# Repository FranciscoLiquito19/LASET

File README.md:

# LASET

Relatório de Laboratório de Sistemas Autónomos: **Sistema de Escrita/Leitura Multi-Protocolo**, com I2C, RS232, RS485, dois CAN FD,
Ethernet, três saídas PWM isoladas e sincronização por PPS/GPS.

Autores: Francisco Liquito e Pedro Ribeiro. Ano letivo: 2026/2027.

## Compilar

O único relatório oficial tem como ficheiro principal
`template_laset/Modelo_LaSET.tex`.
Instalar uma distribuição LaTeX com os pacotes usados nesse ficheiro, além de
`latexmk` e BibTeX. A bibliografia mantém o estilo `unsrt` do template.
Os diagramas vetoriais são compilados diretamente com TikZ/PGF, usando
os estilos comuns de `template_laset/Outros/Estilo_Visual.tex`.

```sh
cd template_laset
mkdir -p build
latexmk -pdf \
  -outdir=build \
  -interaction=nonstopmode \
  -halt-on-error \
  -file-line-error \
  Modelo_LaSET.tex
```

O PDF é gerado em `template_laset/build/Modelo_LaSET.pdf` (caminho relativo à raiz do
repositório). O `latexmk` executa pdfLaTeX, BibTeX e as passagens necessárias
para resolver as citações e os índices.

No VS Code, a receita existente do LaTeX Workshop usa
`"latex-workshop.latex.outDir": "%DIR%/build"` e passa esse diretório ao
`latexmk` através de `-outdir=%OUTDIR%`. Ao compilar o ficheiro principal,
o resultado fica no mesmo caminho indicado acima. O PDF oficial é versionado;
os ficheiros auxiliares de compilação em `build/` são ignorados pelo Git.

A fase do relatório escolhe-se em `template_laset/Outros/Identificacao.tex`
(`\Requisitostrue`, `\Projectotrue`, `\Finalfalse` na fase atual, de Projeto), onde
estão também o título e a data da capa (`\DataRelatorio`, a atualizar em cada entrega).
O Anexo A inclui o esquema elétrico diretamente de `hardware/laset_gateway.pdf`.

## Estrutura

- `template_laset/Modelo_LaSET.tex`: ficheiro principal do único relatório oficial.
- `template_laset/Capitulos/`: conteúdo organizado pelos capítulos oficiais.
- `template_laset/Outros/Identificacao.tex`: fase, título e autores.
- `template_laset/Figuras/`: imagens utilizadas no relatório.
- `template_laset/Figuras/diagramas/`: fontes TikZ dos esquemas e gráficos temporais.
- `template_laset/Anexos/`: conteúdo dos anexos.
- `template_laset/bibliografia.bib`: referências bibliográficas em BibTeX.
- `template_laset/build/`: PDF oficial versionado e auxiliares de compilação ignorados pelo Git.
- `hardware/`: projeto KiCad gerado por código (`hardware/gerador`): esquema, placa de
  quatro camadas (disposição e planos feitos, encaminhamento de sinais por fazer) e lista
  de material em `hardware/bom/bom.csv`; ver o [README do hardware](hardware/README.md).
- `firmware/`: firmware do STM32H7 com FreeRTOS (CMake); ver o [README do firmware](firmware/README.md).
- `.github/workflows/ci.yml`: compila o relatório, verifica o esquema, corre o ERC e o DRC
  do KiCad 9 (com paridade esquema/placa), compila o firmware e corre os testes em cada
  push e pull request.
- `.vscode/settings.json`: configuração de compilação do LaTeX Workshop.

As [notas da revisão](docs/revisao_final.md) incluem os resultados de
validação e um roteiro para leitura conjunta do PDF.

## Apresentação e guião

- [PowerPoint atualizado](apresentacao/output/Apresentacao_LaSET_Integracao_Robotica_Revista.pptx): 10 slides centrados na integração de equipamentos em sistemas robóticos, com fundamentos, estado da arte, casos de utilização, requisitos, arquitetura e verificação prevista.
- [Guião em PDF](apresentacao/output/Guiao_Apresentacao.pdf) e [fonte editável](apresentacao/Guiao_Apresentacao.md): divisão entre Pedro e Francisco Liquito, falas, tempos e perguntas de preparação.

RF17 distingue os quatro pares mínimos obrigatórios com Ethernet dos
percursos adicionais que podem ser definidos e implementados em projeto.
Os critérios de ensaio abrangem todos os percursos efetivamente definidos.

A versão de 29 de outubro acompanha um cenário ilustrativo com motor,
bateria e sensor. A reutilização em diferentes sistemas é um objetivo;
funcionamento em óleo e sob pressão permanece uma possibilidade futura,
com condições e validação por definir. O guião acompanha esta versão,
com Pedro nos slides 1 a 5 e Francisco Liquito nos slides 6 a 10,
numa duração de ensaio de cerca de nove minutos.

## Trabalhar em conjunto

Após receber acesso ao repositório, clonar o projeto:

```sh
git clone https://github.com/FranciscoLiquito19/LASET.git
cd LASET
```

Na primeira vez, em cada computador, configurar o autor dos commits (sem isto aparecem
commits com autor «unknown»):

```sh
git config user.name "Nome Apelido"
git config user.email "email@exemplo.pt"
```

Antes de começar uma alteração, atualizar a cópia local e criar um ramo:

```sh
git pull --ff-only
git switch -c descricao-da-alteracao
```

Depois de editar e compilar, guardar apenas os ficheiros pretendidos e publicar o ramo:

```sh
git add template_laset/ hardware/ README.md
git commit -m "Descrever a alteração"
git push -u origin descricao-da-alteracao
```

No GitHub, abrir um pull request para rever e integrar a alteração no ramo principal
(`master`). Só integrar depois de a verificação automática (CI) passar. Usar um nome diferente para cada novo ramo.

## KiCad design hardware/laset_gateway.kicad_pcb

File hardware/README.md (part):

# Hardware do gateway LASET

Projeto KiCad do gateway multiprotocolo. O esquema é **gerado por código** a partir de
`gerador/`: cada folha é um ficheiro Python com os componentes, os valores e a rede de
cada pino. Assim cada alteração fica revista em PR, como o relatório.

## Abrir o projeto (esquema e placa)

1. Abrir `laset_gateway.kicad_pro` no KiCad (8 ou 9). Se perguntar se quer atualizar o
   formato dos ficheiros, aceitar: o gerador escreve no formato do KiCad 6/7.
2. No editor de esquemas, a folha raiz mostra uma caixa por folha. Duplo clique entra
   na folha.
3. As ligações são feitas por **etiquetas** (texto junto a cada pino) e por símbolos de
   alimentação (GND, +5V, +3V3). Dois pinos com a mesma etiqueta estão ligados.
   Etiquetas com forma de seta são globais e ligam entre folhas.

## Verificar

1. `python3 -I gerador/verificar.py` (precisa do `kicad-cli`): exporta a netlist e falha se
   houver redes com um só pino ou sinais globais que não saem da folha onde nascem.
   Apanha etiquetas mal escritas e pinos esquecidos.
2. No KiCad: `Inspecionar > Verificador de regras elétricas > Executar ERC`. Os pinos sem
   ligação devem ser só os marcados com cruz (NC do LM5177, HO1_LL/HO2_LL, GPIO livres do
   MCU, LEDs do RJ45, sinais auxiliares dos transceivers). Qualquer outro erro deve ser
   reportado. O ERC não corre na linha de comandos do KiCad 7; no 8 ou 9:
   `kicad-cli sch erc laset_gateway.kicad_sch`.

## Regenerar depois de mudar o código

```sh
cd hardware/gerador
python3 -I gerar.py
python3 -I verificar.py
kicad-cli sch export pdf -o ../laset_gateway.pdf ../laset_gateway.kicad_sch
```

O Anexo A do relatório lê este PDF diretamente; basta recompilar o relatório.

O `gerar.py` recusa referências repetidas entre folhas. Não editar à mão os
`.kicad_sch` gerados: as alterações perdem-se na próxima geração. Arrumar a posição dos
componentes na interface é seguro só depois de congelarmos o gerador (fase de layout).

## Placa de circuito impresso (`laset_gateway.kicad_pcb`)

Também é gerada por código, em dois passos, a partir do esquema:

```sh
cd hardware/gerador
python3 pcb.py       # placa, disposição, planos e regras (refaz a placa de raiz)
python3 fanout.py    # vias dos pinos de massa e alimentação para os planos
python3 curtas.py    # rascunho: ligações de sinal curtas (F.Cu, ou B.Cu com duas vias)
python3 encaminhar.py   # rascunho: encaminhador em grelha (A*) para o resto, com vias
```

Ordem usada para a placa atual (refeita a 25 e 26/11 depois da revisão independente):

```sh
python3 pcb.py && python3 fanout.py      # 302 ligações por fazer
python3 pf.py                            # encaminhamento por congestionamento negociado (~60 min): 80
python3 encaminhar.py && FINO=1 python3 encaminhar.py               # 28 -> 21
VIA=0.5 python3 interior.py              # F.Cu + In2 (sinais lentos) e F/B com HV: 21 -> 16
python3 melhorar.py <base>               # pesquisa local (base = placa depois de fanout.py): 16 -> 12
VIA=0.5 BASE=<base> python3 interior.py  # com arranque: 12 -> 11
# fecho por coordenadas e arrancar_e_ordenar() (ver abaixo): 11 -> 0
python3 serigrafia.py                    # referências sem sobreposição e nome dos conectores
# 26/11, depois da revisão:
python3 vias_pad.py && REDUZIR=1 python3 vias_pad.py   # vias fora dos pads: 90 -> 12
python3 baixo.py C62:U5.4 C63:U5.4 C61:U5.3            # desacoplamento do U5 para B.Cu
# VCAP do STM32 (C34, C35) para B.Cu, arrancando e voltando a encaminhar as redes à volta
python3 limpar.py                        # retira pistas com uma ponta solta
python3 pilha.py                         # pilha JLC04161H-7628 no ficheiro da placa
python3 vista3d.py                       # texturas e componentes para hardware/3d/index.html
```

As últimas 11 foram fechadas com pistas e vias postas por coordenadas (afastamento
verificado à mão e depois pelo DRC) ou arrancando e voltando a encaminhar só as redes
vizinhas:

- LM5177: SW2 do pino ao C10 e à zona SW2 por B.Cu, à volta da diagonal do HO2; LA, EN e VIN
  pelo `interior.py` com a área `lm5177` (ver abaixo).
- LAN8742A: via de 0,5 mm do +3V3 do pino 30.25 em (79,1; 30,4), com o GND do C41 a partilhar
  a via do C48; NRST, TX_EN e TXD0 descem em paralelo pelo corredor entre C44 e C42; TXP em
  F.Cu entre RXN e TXN até baixo do R37 e depois por B.Cu entre as resistências de terminação
  (a via do TXN desceu 0,35 mm para lhe dar passagem). R32 saiu do esquema: o REGOFF tem
  pull-down interno e a flutuar o regulador de 1,2 V fica ligado (folha do LAN8742A, 3.7.3.2).
- STM32: I2C1_SCL e GPS_TX com o vizinho (SDA, RX) arrancado e encaminhado depois.
- ETH_REF_CLK: tem 33 Ω em série junto ao PHY (R94). Ao refazer a zona do VCAP (26/11)
  saiu de In2: passa agora por F.Cu (37 mm) e B.Cu (3 mm), com 4 vias.

Área `lm5177`: área de regra sem restrições à volta do LM5177 e dos seus passivos (x 30 a
50, y 26 a 42). Lá dentro a classe HV usa 0,15 mm em vez de 0,6 mm (`.kicad_dru`): sob
máscara de solda, 0,13 mm chegam até 100 V (IPC-2221B, B4). O `interior.py` usa o mesmo
afastamento na grelha.

O `interior.py` usa a camada In2 (plano de 3,3 V) para sinais lentos: cada pista em In2
recorta o plano. Não podem ir para In2 as classes HV e P5V (nós de comutação e potência), a
classe ETH (pares) nem o REF_CLK, a não ser por exceção explícita. As vias de saída são de
0,5/0,2 mm (anel de 0,15 mm) com pelo menos 0,8 mm entre centros. Estão em In2: GPS_TX
(35 mm), GPS_RX (27 mm), CAN1_TX (27 mm), I2C_OE (19 mm), RS485_TX (7 mm) e RBIAS (4 mm),
todos lentos (UART, CAN a 1 Mbit/s no máximo, níveis estáticos). Com a pilha JLC04161H-7628
(`pilha.py`), In2 fica a 0,21 mm de B.Cu e a 1,07 mm de In1: a referência destas pistas é o
plano de 3,3 V à volta e o cobre de B.Cu, não o plano de massa.

Vias e pads (`vias_pad.py`, 26/11): uma via não tapada dentro de um pad, ou encostada a ele,
puxa a solda para o furo e a junta fica fraca. Os encaminhadores deixaram 90 assim; 78 foram
mudadas para o sítio livre mais perto (fora do pad, 0,1 mm de folga) com uma pista curta, 7
delas com 0,5/0,2 mm para caber. Ficam 11 sem lugar, mesmo com pistas em L e 5 mm de busca
(`EM_L=1 REDUZIR=1`): VCC do LM5177, os VISOOUT e o RS485 do lado isolado do U7, CANH1 no D4,
VDDCR no C44, PWM_FALHA no R86 e o +3V3 do U6. Na encomenda, pedir vias cheias e tapadas
("Epoxy Filled & Capped"), que resolve estas 11 sem mexer na placa. Uma via perto de um pad
sem lhe tocar fica tapada pela máscara (é o normal no KiCad) e não conta. As vias dos pads
térmicos (Q1 a Q4) ficam, como é normal.

Desacoplamento em B.Cu (`baixo.py`, 26/11): os condensadores que estavam longe do pino
passaram para a face de baixo, por baixo dele, com uma via de 0,6/0,3 mm ao pino e outra ao
plano de massa: C34 e C35 (VCAP do STM32) de 8,3 e 7,2 mm para 1,5 e 1,0 mm; C61, C62 e C63
(U5) de 6,7, 9,2 e 11,5 mm para 2,5, 1,5 e 1,0 mm. São as únicas 5 peças em B.Cu, o que
obriga à montagem Standard da JLCPCB (duas faces).

O `serigrafia.py` corre uma vez, no fim: põe cada referência (1,0 mm de altura e 0,15 mm de
traço, o que a JLCPCB recomenda) no sítio livre mais perto da peça, sem tocar em pads,
noutras linhas nem no bordo, e esconde as que não cabem (36 na placa atual, passivos em zonas
apertadas). Acrescenta o nome de cada conector
(VIN, ETH, SWD, RS232, I2C1, I2C2, GPS, CAN1, CAN2, RS485, PWM) e desloca o bloco de texto
LASET se tocar em alguma peça. Recusa correr numa placa que já tenha os nomes.

Visualização 3D: `python3 vista3d.py` gera as texturas das duas faces e a lista de
componentes para `3d/index.html` (three.js; abre-se com `python3 -m http.server` na pasta
`3d`). Os footprints têm os modelos 3D do KiCad (o do LM5177 usa o do TSSOP-38), por isso
no KiCad basta `Ver > Visualizador 3D` (Alt+3); se o KiCad 9 não encontrar os modelos,
`Ferramentas > Atualizar footprints a partir da biblioteca` corrige o caminho.

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
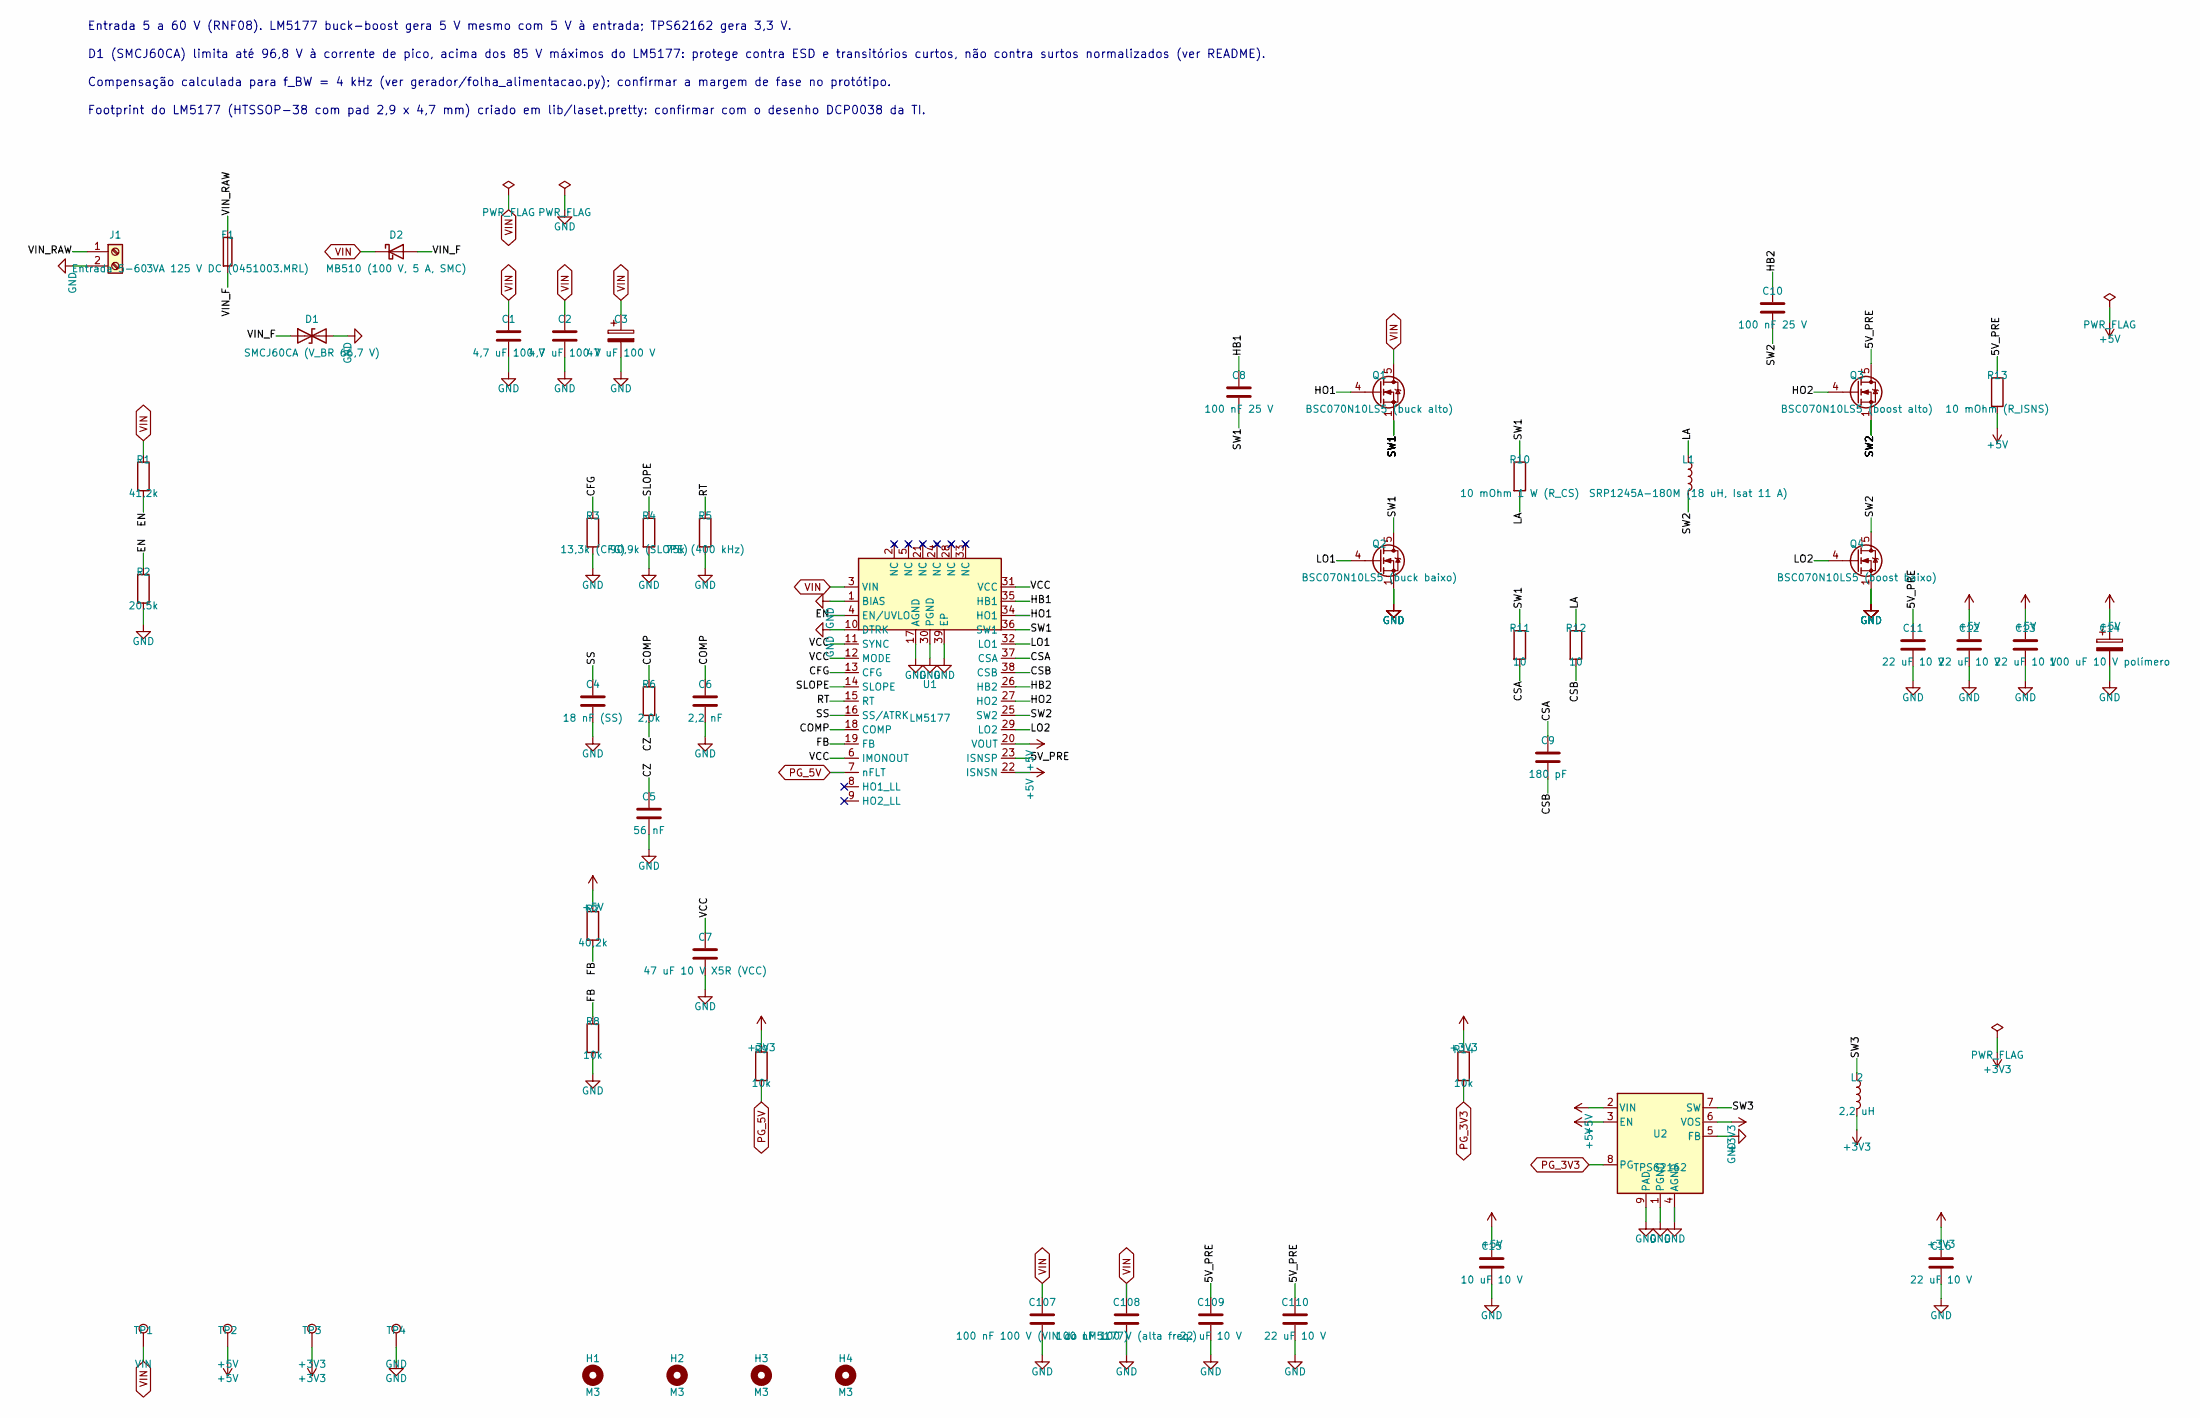
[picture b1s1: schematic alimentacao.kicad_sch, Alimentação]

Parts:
C1, C2: 4,7 uF 100 V; C_1210_3225Metric
C3: 47 uF 100 V; CP_Elec_8x10
C4: 18 nF (SS); C_0603_1608Metric
C5: 56 nF; C_0603_1608Metric
C6: 2,2 nF; C_0603_1608Metric
C7: 47 uF 10 V X5R (VCC); C_1206_3216Metric
C8, C10: 100 nF 25 V; C_0603_1608Metric
C9: 180 pF; C_0603_1608Metric
C11, C12, C13, C16, C109, C110: 22 uF 10 V; C_1206_3216Metric
C14: 100 uF 10 V polímero; CP_Elec_6.3x7.7
C15: 10 uF 10 V; C_0603_1608Metric
C107: 100 nF 100 V (VIN do LM5177); C_0603_1608Metric
C108: 100 nF 100 V (alta freq.); C_0603_1608Metric
D1: SMCJ60CA (V_BR 66,7 V); D_SMC
D2: MB510 (100 V, 5 A, SMC); D_SMC
F1: 3 A 125 V DC (0451003.MRL); Fuse_Littelfuse-NANO2-451_453
H1, H2, H3, H4: M3; MountingHole_3.2mm_M3
J1: Entrada 5-60 V; TerminalBlock_Phoenix_MKDS-1,5-2_1x02_P5.00mm_Horizontal
L1: SRP1245A-180M (18 uH, Isat 11 A); L_Bourns_SRP1245A
L2: 2,2 uH; L_Bourns_SRN6045TA
Q1: BSC070N10LS5 (buck alto); TDSON-8-1
Q2: BSC070N10LS5 (buck baixo); TDSON-8-1
Q3: BSC070N10LS5 (boost alto); TDSON-8-1
Q4: BSC070N10LS5 (boost baixo); TDSON-8-1
R1: 41,2k; R_0603_1608Metric
R2: 20,5k; R_0603_1608Metric
R3: 13,3k (CFG); R_0603_1608Metric
R4: 90,9k (SLOPE); R_0603_1608Metric
R5: 75k (400 kHz); R_0603_1608Metric
R6: 2,0k; R_0603_1608Metric
R7: 40,2k; R_0603_1608Metric
R8, R9, R14: 10k; R_0603_1608Metric
R10: 10 mOhm 1 W (R_CS); R_2512_6332Metric
R11, R12: 10; R_0603_1608Metric
R13: 10 mOhm (R_ISNS); R_2512_6332Metric
TP1: VIN; TestPoint_Pad_D1.5mm
TP2: +5V; TestPoint_Pad_D1.5mm
TP3: +3V3; TestPoint_Pad_D1.5mm
TP4: GND; TestPoint_Pad_D1.5mm
U1: LM5177; HTSSOP-38-1EP_4.4x9.7mm_P0.5mm_EP2.9x4.7mm
U2: TPS62162; WSON-8-1EP_2x2mm_P0.5mm_EP0.9x1.6mm_ThermalVias

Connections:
+3V3: C16.1, L2.2, R9.1, R14.1, TP3.1, U2.6 (VOS); also elsewhere on the board
+5V: C12.1, C13.1, C14.1, C15.1, R7.1, R13.2, TP2.1, U1.20 (VOUT), U1.22 (ISNSN), U2.2 (VIN), U2.3 (EN); also elsewhere on the board
/Alimentação/5V_PRE: C11.1, C109.1, C110.1, Q3.5 (D), R13.1, U1.23 (ISNSP)
/Alimentação/CFG: R3.1, U1.13 (CFG)
/Alimentação/COMP: C6.1, R6.1, U1.18 (COMP)
/Alimentação/CSA: C9.1, R11.2, U1.37 (CSA)
/Alimentação/CSB: C9.2, R12.2, U1.38 (CSB)
/Alimentação/CZ: C5.1, R6.2
/Alimentação/EN: R1.2, R2.1, U1.4 (EN/UVLO)
/Alimentação/FB: R7.2, R8.1, U1.19 (FB)
/Alimentação/HB1: C8.1, U1.35 (HB1)
/Alimentação/HB2: C10.1, U1.26 (HB2)
/Alimentação/HO1: Q1.4 (G), U1.34 (HO1)
/Alimentação/HO2: Q3.4 (G), U1.27 (HO2)
/Alimentação/LA: L1.1, R10.2, R12.1
/Alimentação/LO1: Q2.4 (G), U1.32 (LO1)
/Alimentação/LO2: Q4.4 (G), U1.29 (LO2)
/Alimentação/RT: R5.1, U1.15 (RT)
/Alimentação/SLOPE: R4.1, U1.14 (SLOPE)
/Alimentação/SS: C4.1, U1.16 (SS/ATRK)
/Alimentação/SW1: C8.2, Q1.1 (S), Q1.2 (S), Q1.3 (S), Q2.5 (D), R10.1, R11.1, U1.36 (SW1)
/Alimentação/SW2: C10.2, L1.2, Q3.1 (S), Q3.2 (S), Q3.3 (S), Q4.5 (D), U1.25 (SW2)
/Alimentação/SW3: L2.1, U2.7 (SW)
/Alimentação/VCC: C7.1, U1.6 (IMONOUT), U1.11 (SYNC), U1.12 (MODE), U1.31 (VCC)
/Alimentação/VIN_F: D1.1 (A1), D2.2 (A), F1.2
/Alimentação/VIN_RAW: F1.1, J1.1
GND: C1.2, C2.2, C3.2, C4.2, C5.2, C6.2, C7.2, C11.2, C12.2, C13.2, C14.2, C15.2, C16.2, C107.2, C108.2, C109.2, C110.2, D1.2 (A2), J1.2, Q2.1 (S), Q2.2 (S), Q2.3 (S), Q4.1 (S), Q4.2 (S), Q4.3 (S), R2.2, R3.2, R4.2, R5.2, R8.2, TP4.1, U1.1 (BIAS), U1.10 (DTRK), U1.17 (AGND), U1.30 (PGND), U1.39 (EP), U2.1 (PGND), U2.4 (AGND), U2.5 (FB), U2.9 (PAD); also elsewhere on the board
PG_3V3: R14.2, U2.8 (PG); also elsewhere on the board
PG_5V: R9.2, U1.7 (nFLT); also elsewhere on the board
VIN: C1.1, C2.1, C3.1, C107.1, C108.1, D2.1 (K), Q1.5 (D), R1.1, TP1.1, U1.3 (VIN)

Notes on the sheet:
Entrada 5 a 60 V (RNF08). LM5177 buck-boost gera 5 V mesmo com 5 V à entrada; TPS62162 gera 3,3 V.
D1 (SMCJ60CA) limita até 96,8 V à corrente de pico, acima dos 85 V máximos do LM5177: protege contra ESD e transitórios curtos, não contra surtos normalizados (ver README).
Compensação calculada para f_BW = 4 kHz (ver gerador/folha_alimentacao.py); confirmar a margem de fase no protótipo.
Footprint do LM5177 (HTSSOP-38 com pad 2,9 x 4,7 mm) criado em lib/laset.pretty: confirmar com o desenho DCP0038 da TI.

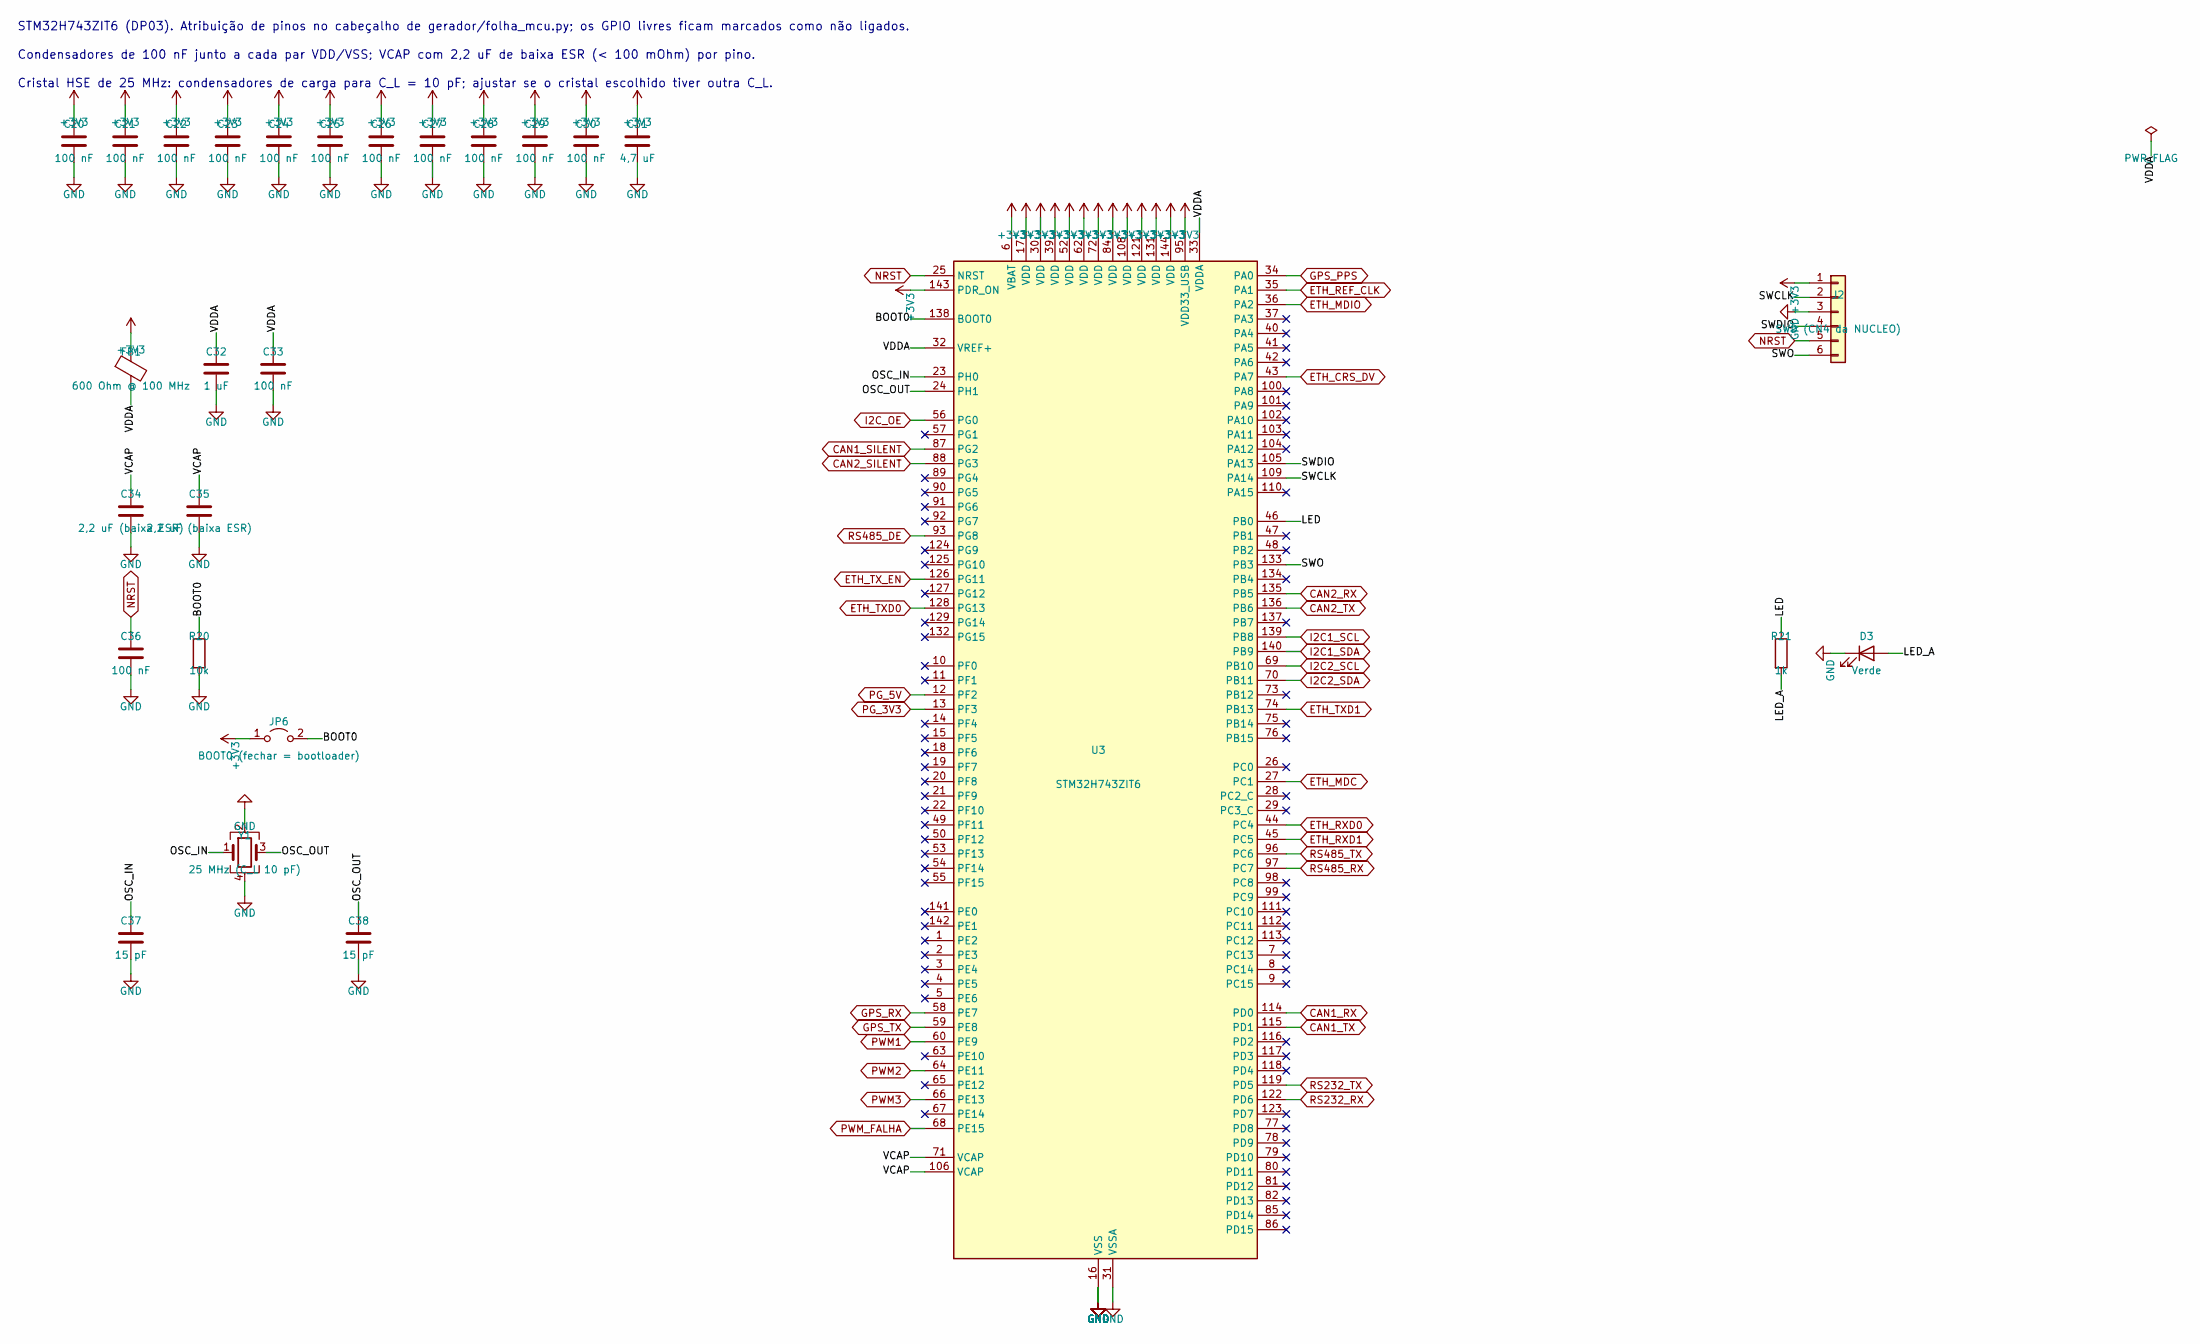
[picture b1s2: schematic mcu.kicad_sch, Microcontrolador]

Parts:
C20, C21, C22, C23, C24, C25, C26, C27, C28, C29, C30, C33, C36: 100 nF; C_0603_1608Metric
C31: 4,7 uF; C_0603_1608Metric
C32: 1 uF; C_0603_1608Metric
C34, C35: 2,2 uF (baixa ESR); C_0805_2012Metric
C37, C38: 15 pF; C_0603_1608Metric
D3: Verde; LED_0603_1608Metric
FB1: 600 Ohm @ 100 MHz; L_0603_1608Metric
J2: SWD (CN4 da NUCLEO); PinHeader_1x06_P2.54mm_Vertical
JP6: BOOT0 (fechar = bootloader); PinHeader_1x02_P2.54mm_Vertical
R20: 10k; R_0603_1608Metric
R21: 1k; R_0603_1608Metric
U3: STM32H743ZIT6; LQFP-144_20x20mm_P0.5mm
Y1: 25 MHz (C_L 10 pF); Crystal_SMD_3225-4Pin_3.2x2.5mm

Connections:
+3V3: C20.1, C21.1, C22.1, C23.1, C24.1, C25.1, C26.1, C27.1, C28.1, C29.1, C30.1, C31.1, FB1.1, J2.1, JP6.1 (A), U3.6 (VBAT), U3.17 (VDD), U3.30 (VDD), U3.39 (VDD), U3.52 (VDD), U3.62 (VDD), U3.72 (VDD), U3.84 (VDD), U3.95 (VDD33_USB), U3.108 (VDD), U3.121 (VDD), U3.131 (VDD), U3.143 (PDR_ON), U3.144 (VDD); also elsewhere on the board
/Microcontrolador/BOOT0: JP6.2 (B), R20.1, U3.138 (BOOT0)
/Microcontrolador/LED: R21.1, U3.46 (PB0)
/Microcontrolador/LED_A: D3.2 (A), R21.2
/Microcontrolador/OSC_IN: C37.1, U3.23 (PH0), Y1.1
/Microcontrolador/OSC_OUT: C38.1, U3.24 (PH1), Y1.3
/Microcontrolador/SWCLK: J2.2, U3.109 (PA14)
/Microcontrolador/SWDIO: J2.4, U3.105 (PA13)
/Microcontrolador/SWO: J2.6, U3.133 (PB3)
/Microcontrolador/VCAP: C34.1, C35.1, U3.71 (VCAP), U3.106 (VCAP)
/Microcontrolador/VDDA: C32.1, C33.1, FB1.2, U3.32 (VREF+), U3.33 (VDDA)
CAN1_RX: U3.114 (PD0); also elsewhere on the board
CAN1_SILENT: U3.87 (PG2); also elsewhere on the board
CAN1_TX: U3.115 (PD1); also elsewhere on the board
CAN2_RX: U3.135 (PB5); also elsewhere on the board
CAN2_SILENT: U3.88 (PG3); also elsewhere on the board
CAN2_TX: U3.136 (PB6); also elsewhere on the board
ETH_CRS_DV: U3.43 (PA7); also elsewhere on the board
ETH_MDC: U3.27 (PC1); also elsewhere on the board
ETH_MDIO: U3.36 (PA2); also elsewhere on the board
ETH_REF_CLK: U3.35 (PA1); also elsewhere on the board
ETH_RXD0: U3.44 (PC4); also elsewhere on the board
ETH_RXD1: U3.45 (PC5); also elsewhere on the board
ETH_TXD0: U3.128 (PG13); also elsewhere on the board
ETH_TXD1: U3.74 (PB13); also elsewhere on the board
ETH_TX_EN: U3.126 (PG11); also elsewhere on the board
GND: C20.2, C21.2, C22.2, C23.2, C24.2, C25.2, C26.2, C27.2, C28.2, C29.2, C30.2, C31.2, C32.2, C33.2, C34.2, C35.2, C36.2, C37.2, C38.2, D3.1 (K), J2.3, R20.2, U3.16 (VSS), U3.31 (VSSA), U3.38 (VSS), U3.51 (VSS), U3.61 (VSS), U3.83 (VSS), U3.94 (VSS), U3.107 (VSS), U3.120 (VSS), U3.130 (VSS), Y1.2, Y1.4; also elsewhere on the board
GPS_PPS: U3.34 (PA0); also elsewhere on the board
GPS_RX: U3.58 (PE7); also elsewhere on the board
GPS_TX: U3.59 (PE8); also elsewhere on the board
I2C1_SCL: U3.139 (PB8); also elsewhere on the board
I2C1_SDA: U3.140 (PB9); also elsewhere on the board
I2C2_SCL: U3.69 (PB10); also elsewhere on the board
I2C2_SDA: U3.70 (PB11); also elsewhere on the board
I2C_OE: U3.56 (PG0); also elsewhere on the board
NRST: C36.1, J2.5, U3.25 (NRST); also elsewhere on the board
PG_3V3: U3.13 (PF3); also elsewhere on the board
PG_5V: U3.12 (PF2); also elsewhere on the board
PWM1: U3.60 (PE9); also elsewhere on the board
PWM2: U3.64 (PE11); also elsewhere on the board
PWM3: U3.66 (PE13); also elsewhere on the board
PWM_FALHA: U3.68 (PE15); also elsewhere on the board
RS232_RX: U3.122 (PD6); also elsewhere on the board
RS232_TX: U3.119 (PD5); also elsewhere on the board
RS485_DE: U3.93 (PG8); also elsewhere on the board
RS485_RX: U3.97 (PC7); also elsewhere on the board
RS485_TX: U3.96 (PC6); also elsewhere on the board

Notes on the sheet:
STM32H743ZIT6 (DP03). Atribuição de pinos no cabeçalho de gerador/folha_mcu.py; os GPIO livres ficam marcados como não ligados.
Condensadores de 100 nF junto a cada par VDD/VSS; VCAP com 2,2 uF de baixa ESR (< 100 mOhm) por pino.
Cristal HSE de 25 MHz: condensadores de carga para C_L = 10 pF; ajustar se o cristal escolhido tiver outra C_L.

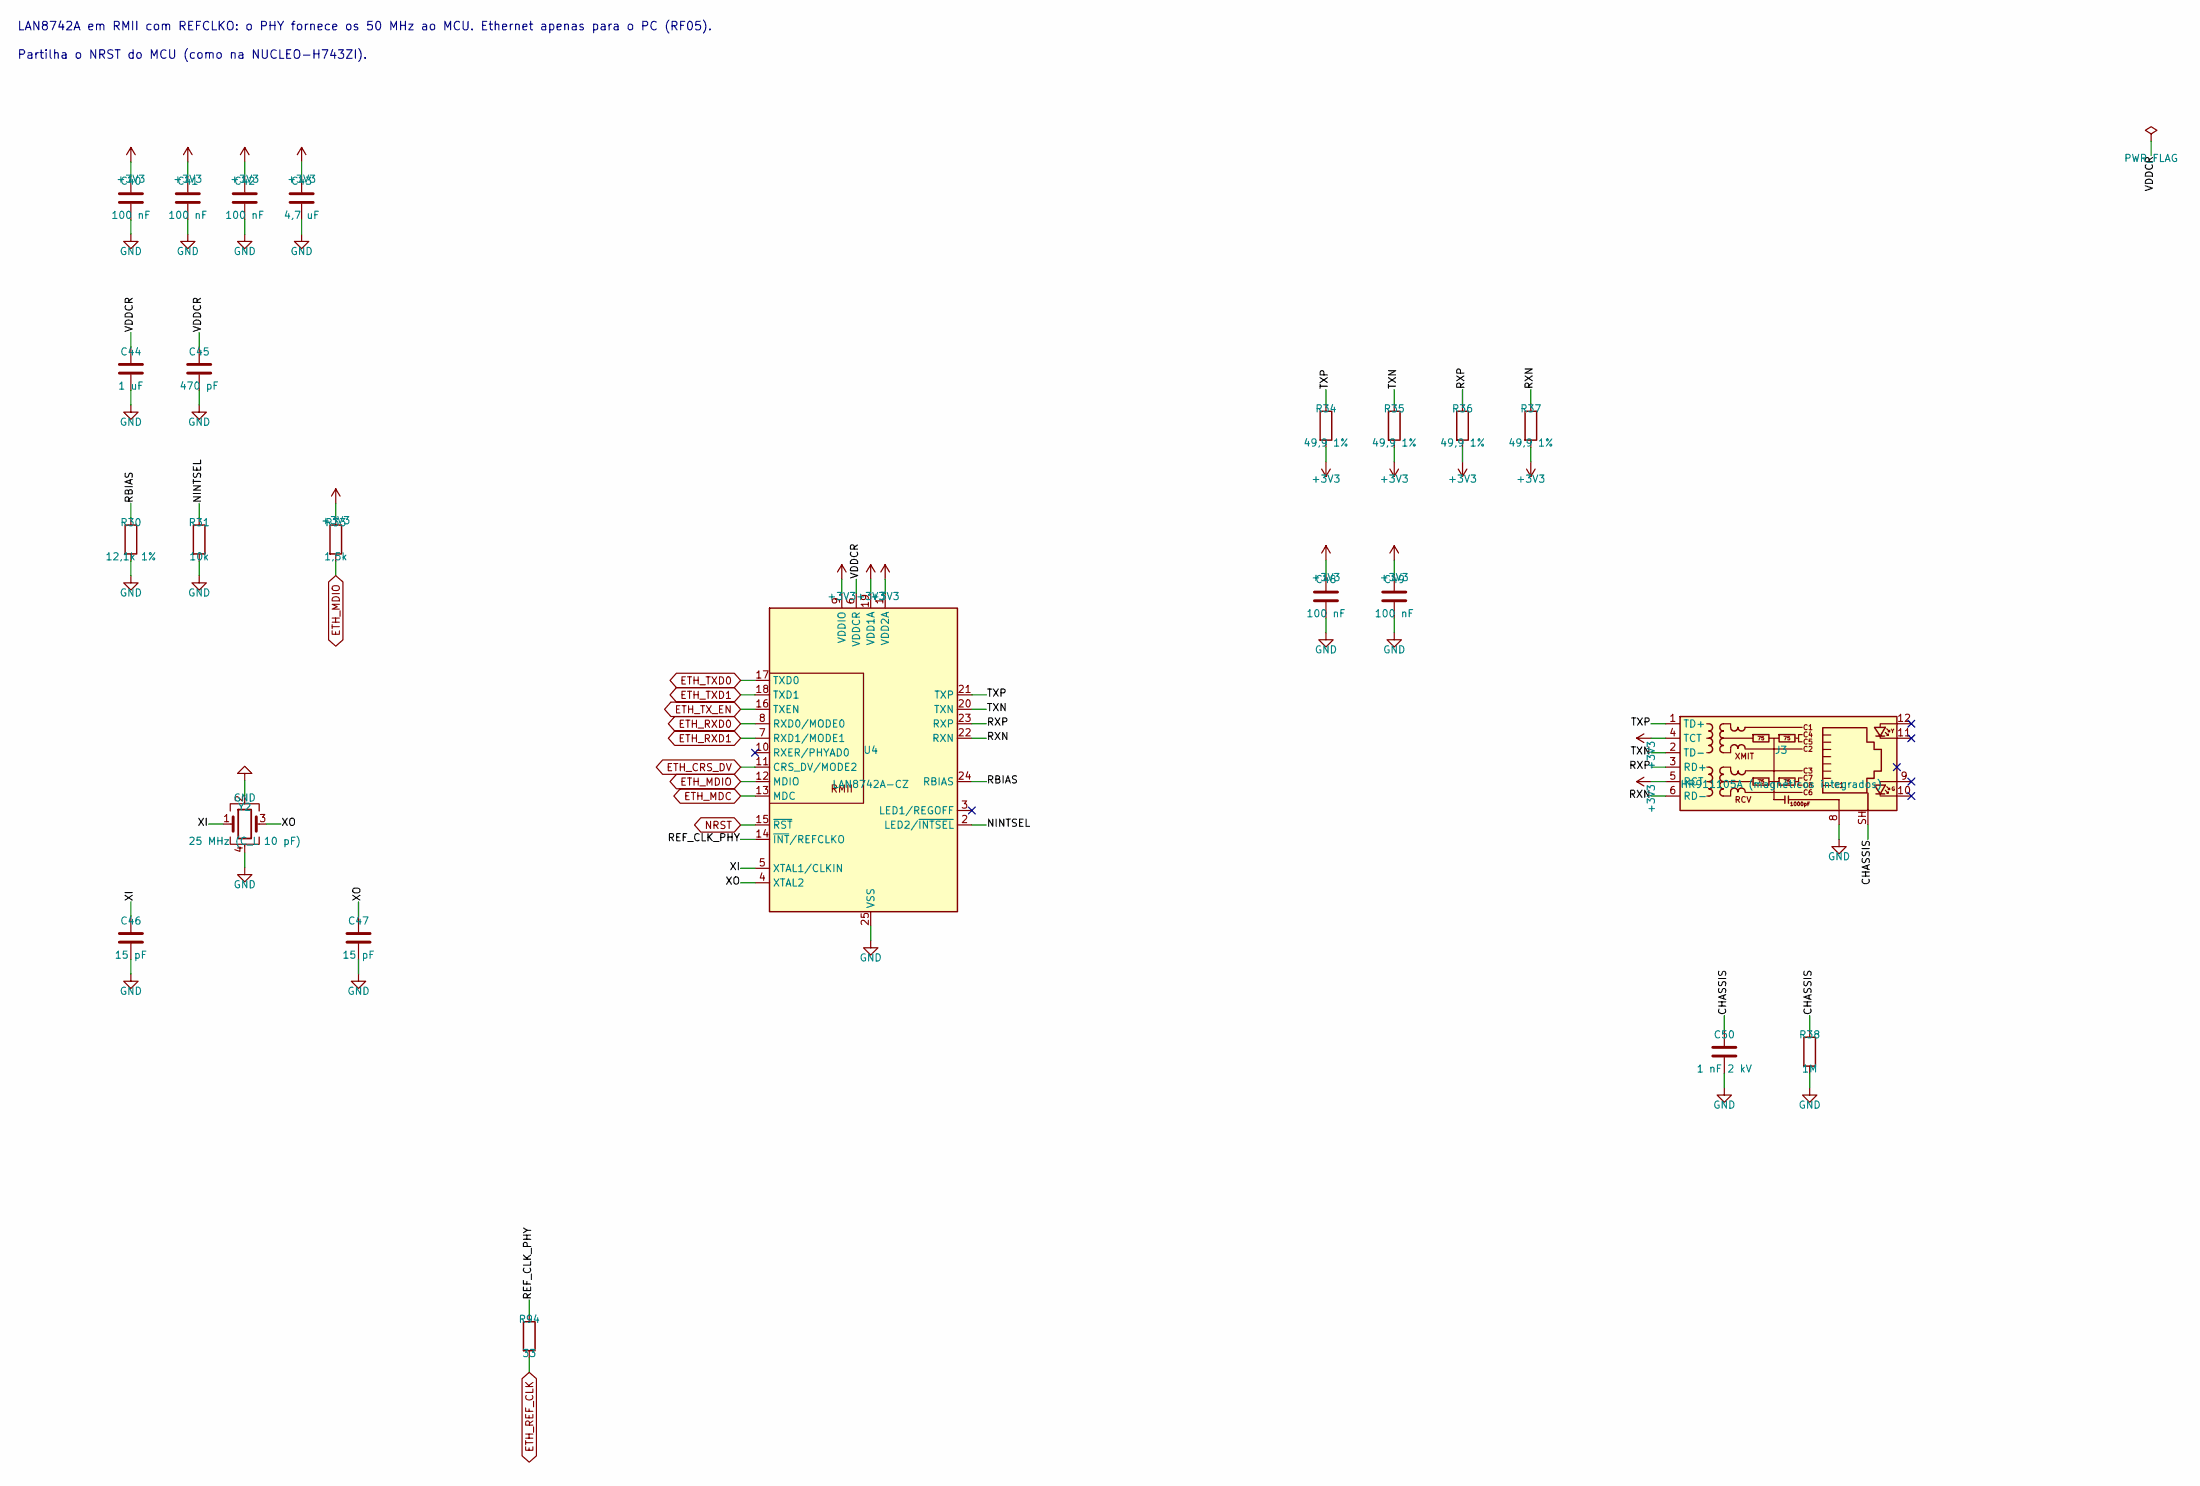
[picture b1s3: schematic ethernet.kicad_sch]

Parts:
C40, C41, C42, C48, C49: 100 nF; C_0603_1608Metric
C43: 4,7 uF; C_0603_1608Metric
C44: 1 uF; C_0603_1608Metric
C45: 470 pF; C_0603_1608Metric
C46, C47: 15 pF; C_0603_1608Metric
C50: 1 nF 2 kV; C_1206_3216Metric
J3: HR911105A (magnéticos integrados); RJ45_Hanrun_HR911105A_Horizontal
R30: 12,1k 1%; R_0603_1608Metric
R31: 10k; R_0603_1608Metric
R33: 1,5k; R_0603_1608Metric
R34, R35, R36, R37: 49,9 1%; R_0603_1608Metric
R38: 1M; R_1206_3216Metric
R94: 33; R_0603_1608Metric
U4: LAN8742A-CZ; VQFN-24-1EP_4x4mm_P0.5mm_EP2.5x2.5mm_ThermalVias
Y2: 25 MHz (C_L 10 pF); Crystal_SMD_3225-4Pin_3.2x2.5mm

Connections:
+3V3: C40.1, C41.1, C42.1, C43.1, C48.1, C49.1, J3.4 (TCT), J3.5 (RCT), R33.1, R34.2, R35.2, R36.2, R37.2, U4.1 (VDD2A), U4.9 (VDDIO), U4.19 (VDD1A); also elsewhere on the board
/Ethernet/CHASSIS: C50.1, J3.SH, R38.1
/Ethernet/NINTSEL: R31.1, U4.2 (LED2/~INTSEL)
/Ethernet/RBIAS: R30.1, U4.24 (RBIAS)
/Ethernet/REF_CLK_PHY: R94.1, U4.14 (~INT/REFCLKO)
/Ethernet/RXN: J3.6 (RD-), R37.1, U4.22 (RXN)
/Ethernet/RXP: J3.3 (RD+), R36.1, U4.23 (RXP)
/Ethernet/TXN: J3.2 (TD-), R35.1, U4.20 (TXN)
/Ethernet/TXP: J3.1 (TD+), R34.1, U4.21 (TXP)
/Ethernet/VDDCR: C44.1, C45.1, U4.6 (VDDCR)
/Ethernet/XI: C46.1, U4.5 (XTAL1/CLKIN), Y2.1
/Ethernet/XO: C47.1, U4.4 (XTAL2), Y2.3
ETH_CRS_DV: U4.11 (CRS_DV/MODE2); also elsewhere on the board
ETH_MDC: U4.13 (MDC); also elsewhere on the board
ETH_MDIO: R33.2, U4.12 (MDIO); also elsewhere on the board
ETH_REF_CLK: R94.2; also elsewhere on the board
ETH_RXD0: U4.8 (RXD0/MODE0); also elsewhere on the board
ETH_RXD1: U4.7 (RXD1/MODE1); also elsewhere on the board
ETH_TXD0: U4.17 (TXD0); also elsewhere on the board
ETH_TXD1: U4.18 (TXD1); also elsewhere on the board
ETH_TX_EN: U4.16 (TXEN); also elsewhere on the board
GND: C40.2, C41.2, C42.2, C43.2, C44.2, C45.2, C46.2, C47.2, C48.2, C49.2, C50.2, J3.8, R30.2, R31.2, R38.2, U4.25 (VSS), Y2.2, Y2.4; also elsewhere on the board
NRST: U4.15 (~RST); also elsewhere on the board

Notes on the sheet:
LAN8742A em RMII com REFCLKO: o PHY fornece os 50 MHz ao MCU. Ethernet apenas para o PC (RF05).
Partilha o NRST do MCU (como na NUCLEO-H743ZI).
